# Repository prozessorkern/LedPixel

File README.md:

# LedPixel
Small devices to drive up to 10W RGB LEDs by DMX
There might be a possibility to use them als a LED Wall/Display with extreme high power :)

## there might be several versions of the pcb (and Firmware)
* a dev board version with an ATmega8 with USB Bootloader, a dip Switch and some additional Interfaces
* a RGBW version with 4 LED Drivers an a STM32 Controller with 16 bit PWM, an faster RS485 than DMX and an additional SPI Interface for addressing multiple devices
* a board for an external LED

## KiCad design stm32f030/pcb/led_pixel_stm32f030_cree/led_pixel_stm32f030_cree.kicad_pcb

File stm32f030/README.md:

# LedPixel stm32f030

* a more powerful version with 4 chanels for RGBW LEDs
* designed with a backplane bus for dynamic adressing of multiple devices
* capable of 16 bit pwm for better resolution

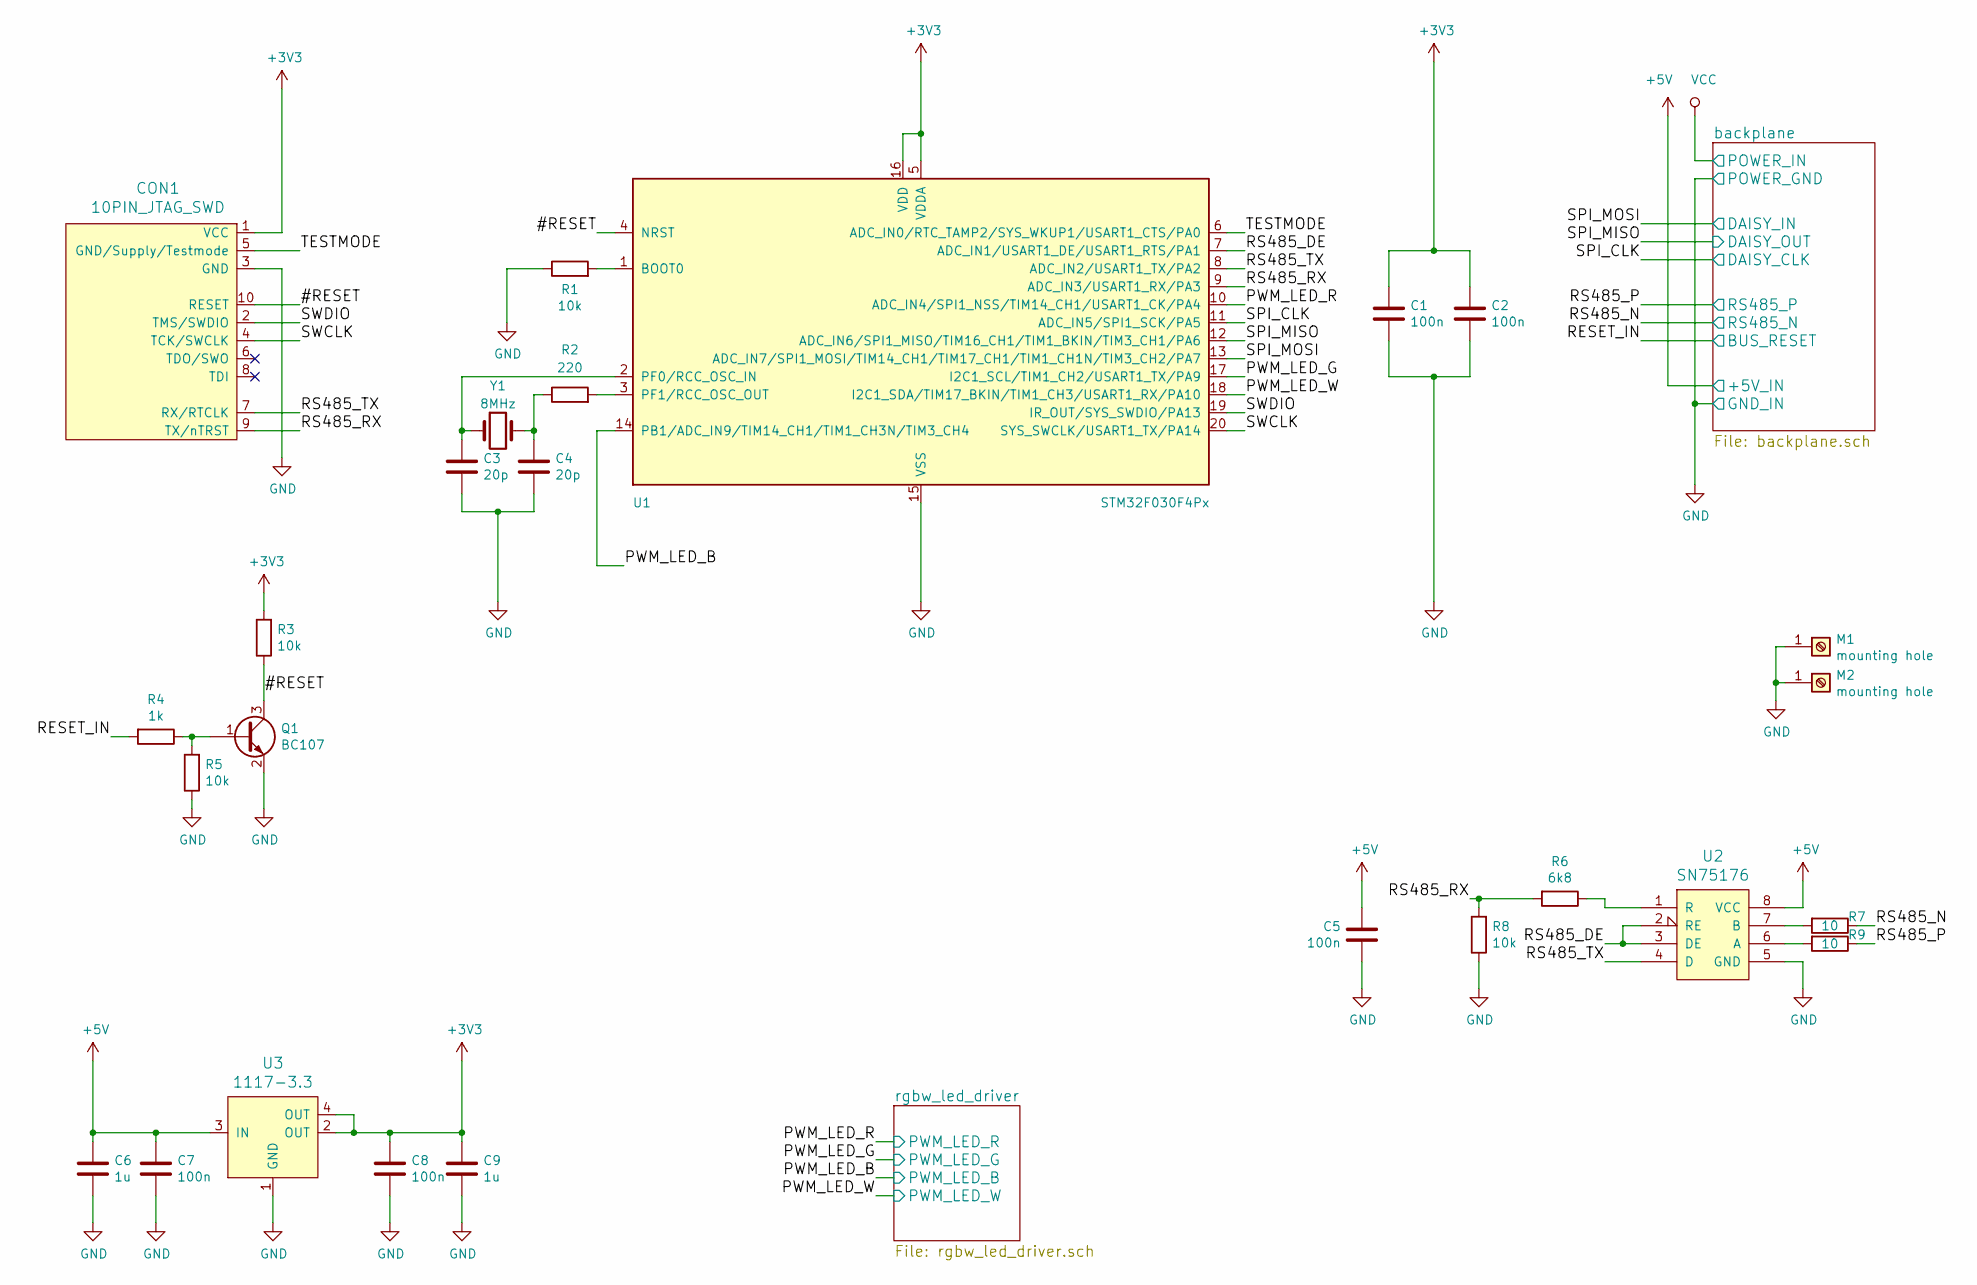
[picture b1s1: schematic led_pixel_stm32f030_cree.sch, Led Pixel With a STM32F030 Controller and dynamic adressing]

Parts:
C1, C2, C5, C7, C8: 100n; C_0603_HandSoldering
C3, C4: 20p; C_0603_HandSoldering
C6, C9: 1u; C_0603_HandSoldering
CON1: 10PIN_JTAG_SWD; TC2050-IDC
M1, M2: mounting hole; MountingHole_3.2mm_M3_Pad_Via
Q1: BC107; SOT-23
R1, R3, R5, R8: 10k; R_0603_HandSoldering
R2: 220; R_0603_HandSoldering
R4: 1k; R_0603_HandSoldering
R6: 6k8; R_0603_HandSoldering
R7, R9: 10; R_0603_HandSoldering
U1: STM32F030F4Px; TSSOP-20_4.4x6.5mm_Pitch0.65mm
U2: SN75176; SO-8
U3: 1117-3.3; SOT-223
Y1: 8MHz; Crystal_SMD_HC49-SD

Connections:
+3V3: C1.1, C2.1, C8.1, C9.1, CON1.1 (VCC), R3.2, U1.5 (VDDA), U1.16 (VDD), U3.2 (OUT), U3.4 (OUT)
+5V: C5.1, C6.1, C7.1, U2.8 (VCC), U3.3 (IN); also elsewhere on the board
/#RESET: CON1.10 (RESET), Q1.3 (C), R3.1, U1.4 (NRST)
/PWM_LED_B: U1.14 (PB1/ADC_IN9/TIM14_CH1/TIM1_CH3N/TIM3_CH4); also elsewhere on the board
/PWM_LED_G: U1.17 (I2C1_SCL/TIM1_CH2/USART1_TX/PA9); also elsewhere on the board
/PWM_LED_R: U1.10 (ADC_IN4/SPI1_NSS/TIM14_CH1/USART1_CK/PA4); also elsewhere on the board
/PWM_LED_W: U1.18 (I2C1_SDA/TIM17_BKIN/TIM1_CH3/USART1_RX/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); also elsewhere on the board
/RESET_IN: R4.2; also elsewhere on the board
/RS485_DE: U1.7 (ADC_IN1/USART1_DE/USART1_RTS/PA1), U2.2 (RE), U2.3 (DE)
/RS485_N: R7.1; also elsewhere on the board
/RS485_P: R9.1; also elsewhere on the board
/RS485_RX: CON1.9 (TX/nTRST), R6.2, R8.2, U1.9 (ADC_IN3/USART1_RX/PA3)
/RS485_TX: CON1.7 (RX/RTCLK), U1.8 (ADC_IN2/USART1_TX/PA2), U2.4 (D)
/SPI_CLK: U1.11 (ADC_IN5/SPI1_SCK/PA5); also elsewhere on the board
/SPI_MISO: U1.12 (ADC_IN6/SPI1_MISO/TIM16_CH1/TIM1_BKIN/T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); also elsewhere on the board
/SPI_MOSI: U1.13 (ADC_IN7/SPI1_MOSI/TIM14_CH1/TIM17_CH1/T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); also elsewhere on the board
/SWCLK: CON1.4 (TCK/SWCLK), U1.20 (SYS_SWCLK/USART1_TX/PA14)
/SWDIO: CON1.2 (TMS/SWDIO), U1.19 (IR_OUT/SYS_SWDIO/PA13)
/TESTMODE: CON1.5 (GND/Supply/Testmode), U1.6 (ADC_IN0/RTC_TAMP2/SYS_WKUP1/USART1_CTS/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)
GND: C1.2, C2.2, C3.2, C4.2, C5.2, C6.2, C7.2, C8.2, C9.2, CON1.3 (GND), M1.1, M2.1, Q1.2 (E), R1.1, R5.1, R8.1, U1.15 (VSS), U2.5 (GND), U3.1 (GND); also elsewhere on the board
unnamed: C3.1, U1.2 (PF0/RCC_OSC_IN), Y1.1
unnamed: C4.1, R2.1, Y1.2
unnamed: Q1.1 (B), R4.1, R5.2
unnamed: R1.2, U1.1 (BOOT0)
unnamed: R2.2, U1.3 (PF1/RCC_OSC_OUT)
unnamed: R6.1, U2.1 (R)
unnamed: R7.2, U2.7 (B)
unnamed: R9.2, U2.6 (A)

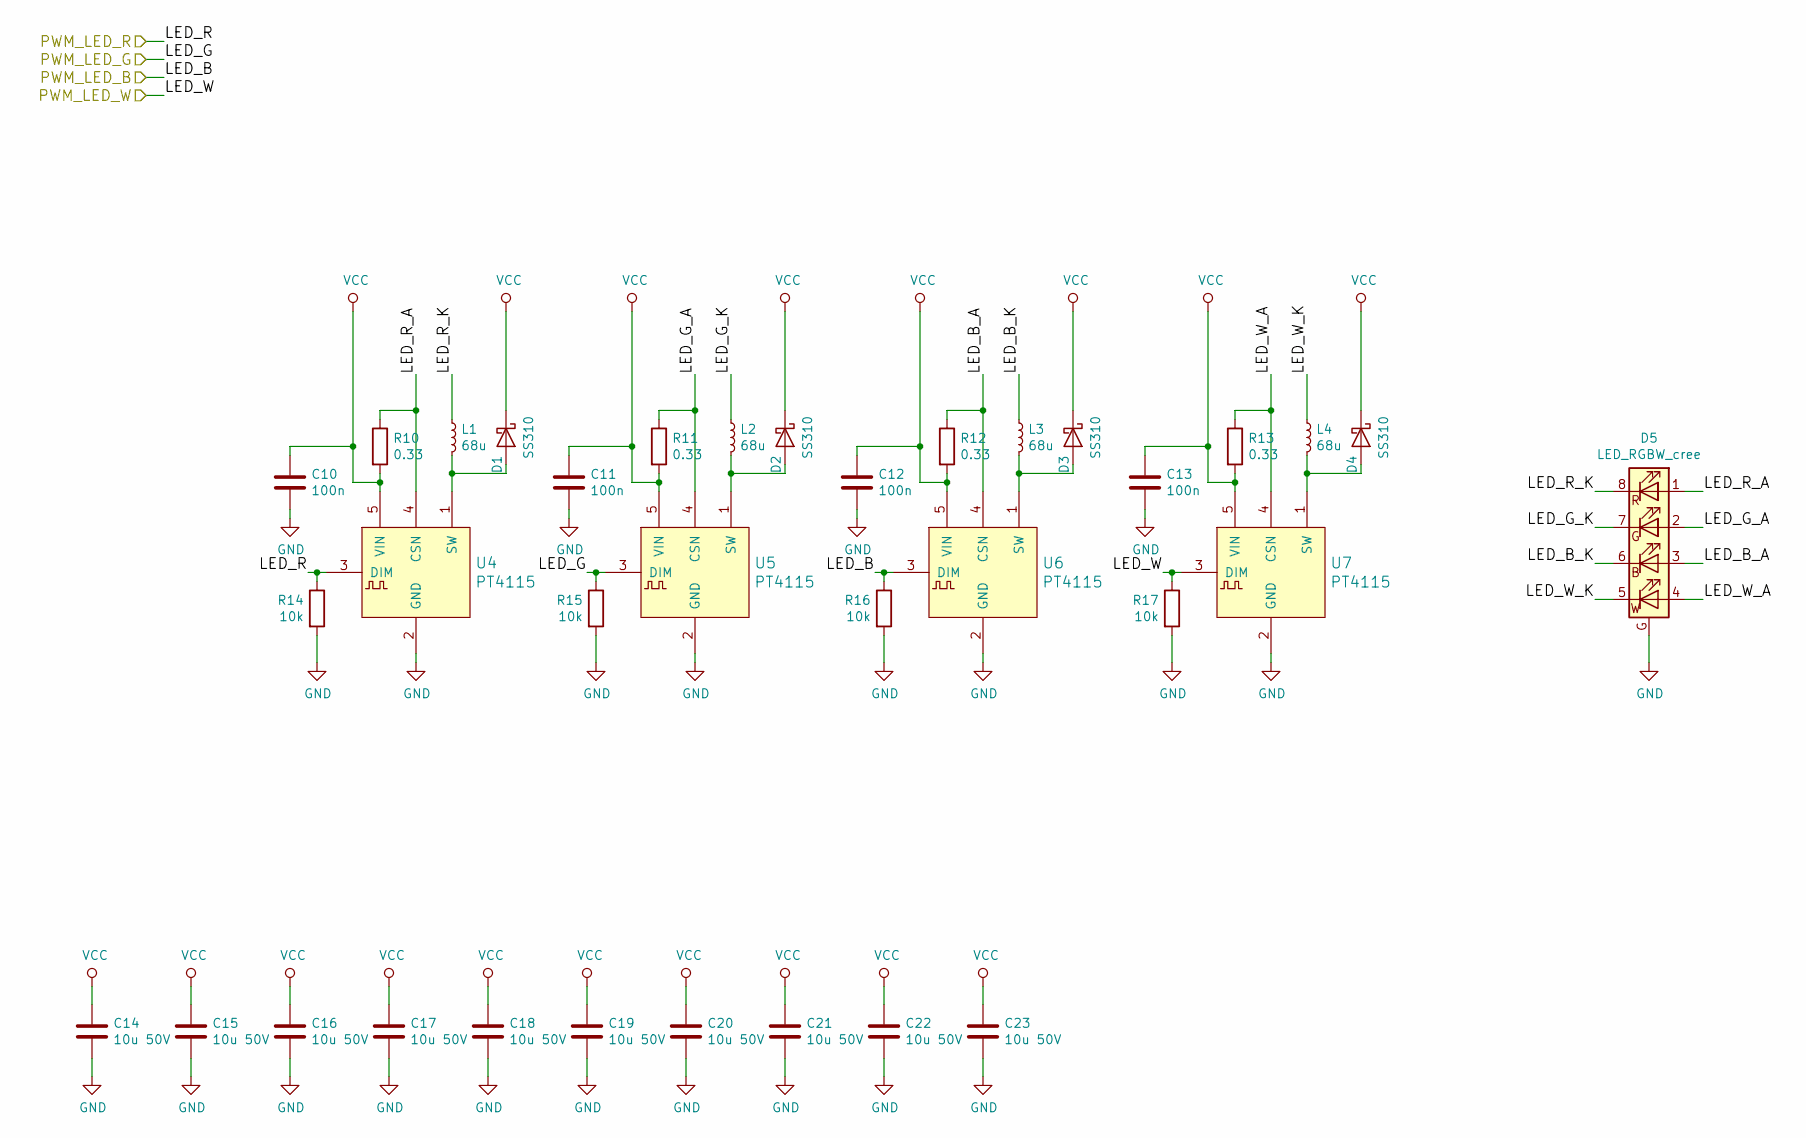
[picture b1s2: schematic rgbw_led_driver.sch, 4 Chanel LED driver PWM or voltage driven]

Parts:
C10, C11, C12, C13: 100n; C_0805_HandSoldering
C14, C15, C16, C17, C18, C19, C20, C21, C22, C23: 10u 50V; C_1210
D1, D2, D3, D4: SS310; D_SMA_Standard
D5: LED_RGBW_cree; LED_SMD_CREE_XM-L_4Color
L1, L2, L3, L4: 68u; Choke_SMD_4.5x4x3.2
R10, R11, R12, R13: 0.33; R_1206_HandSoldering
R14, R15, R16, R17: 10k; R_0603_HandSoldering
U4, U5, U6, U7: PT4115; SOT89-5_Housing_Handsoldering

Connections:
/PWM_LED_B: R16.1, U6.3 (DIM); also elsewhere on the board
/PWM_LED_G: R15.1, U5.3 (DIM); also elsewhere on the board
/PWM_LED_R: R14.1, U4.3 (DIM); also elsewhere on the board
/PWM_LED_W: R17.1, U7.3 (DIM); also elsewhere on the board
/rgbw_led_driver/LED_B_A: D5.3 (BK), R12.1, U6.4 (CSN)
/rgbw_led_driver/LED_B_K: D5.6 (BA), L3.1
/rgbw_led_driver/LED_G_A: D5.2 (GK), R11.1, U5.4 (CSN)
/rgbw_led_driver/LED_G_K: D5.7 (GA), L2.1
/rgbw_led_driver/LED_R_A: D5.1 (RK), R10.1, U4.4 (CSN)
/rgbw_led_driver/LED_R_K: D5.8 (RA), L1.1
/rgbw_led_driver/LED_W_A: D5.4 (WK), R13.1, U7.4 (CSN)
/rgbw_led_driver/LED_W_K: D5.5 (WA), L4.1
GND: C10.2, C11.2, C12.2, C13.2, C14.2, C15.2, C16.2, C17.2, C18.2, C19.2, C20.2, C21.2, C22.2, C23.2, D5.G (Thermal_Pad), R14.2, R15.2, R16.2, R17.2, U4.2 (GND), U5.2 (GND), U6.2 (GND), U7.2 (GND); also elsewhere on the board
unnamed: D1.2 (A), L1.2, U4.1 (SW)
unnamed: D2.2 (A), L2.2, U5.1 (SW)
unnamed: D3.2 (A), L3.2, U6.1 (SW)
unnamed: D4.2 (A), L4.2, U7.1 (SW)
VCC: C10.1, C11.1, C12.1, C13.1, C14.1, C15.1, C16.1, C17.1, C18.1, C19.1, C20.1, C21.1, C22.1, C23.1, D1.1 (K), D2.1 (K), D3.1 (K), D4.1 (K), R10.2, R11.2, R12.2, R13.2, U4.5 (VIN), U5.5 (VIN), U6.5 (VIN), U7.5 (VIN); also elsewhere on the board

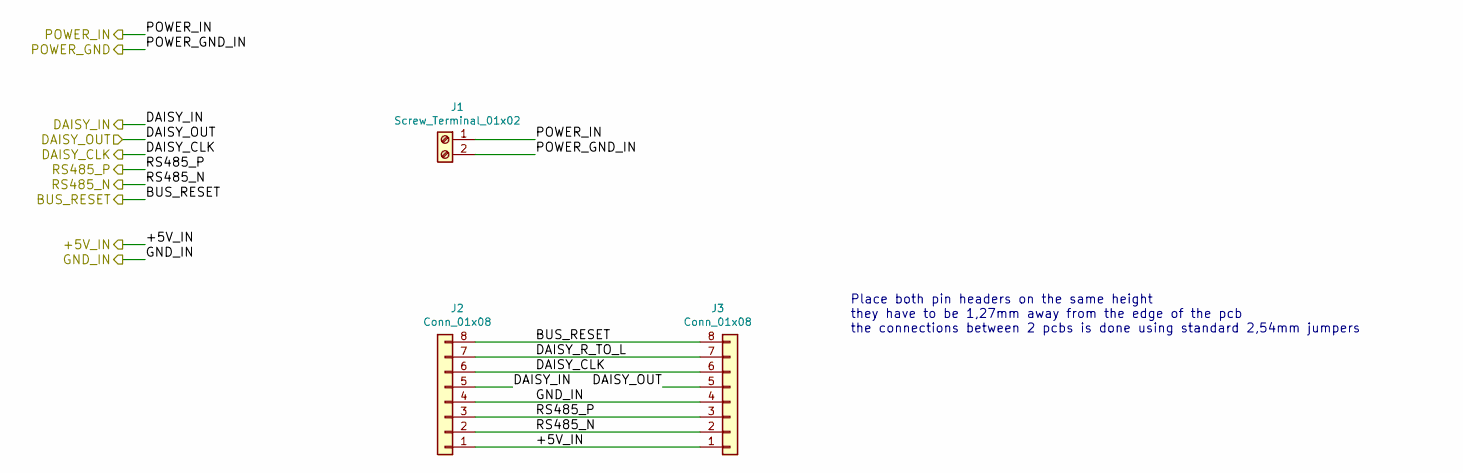
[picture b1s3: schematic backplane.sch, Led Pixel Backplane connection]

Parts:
J1: Screw_Terminal_01x02; AK300-2
J2, J3: Conn_01x08; Pin_Header_Straight_1x08_Pitch2.54mm

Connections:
+5V: J2.1, J3.1; also elsewhere on the board
/RESET_IN: J2.8, J3.8; also elsewhere on the board
/RS485_N: J2.2, J3.2; also elsewhere on the board
/RS485_P: J2.3, J3.3; also elsewhere on the board
/SPI_CLK: J2.6, J3.6; also elsewhere on the board
/SPI_MISO: J3.5; also elsewhere on the board
/SPI_MOSI: J2.5; also elsewhere on the board
/backplane/DAISY_R_TO_L: J2.7, J3.7
GND: J1.2, J2.4, J3.4; also elsewhere on the board
VCC: J1.1; also elsewhere on the board

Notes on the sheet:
Place both pin headers on the same height they have to be 1,27mm away from the edge of the pcb the connections between 2 pcbs is done using standard 2,54mm jumpers

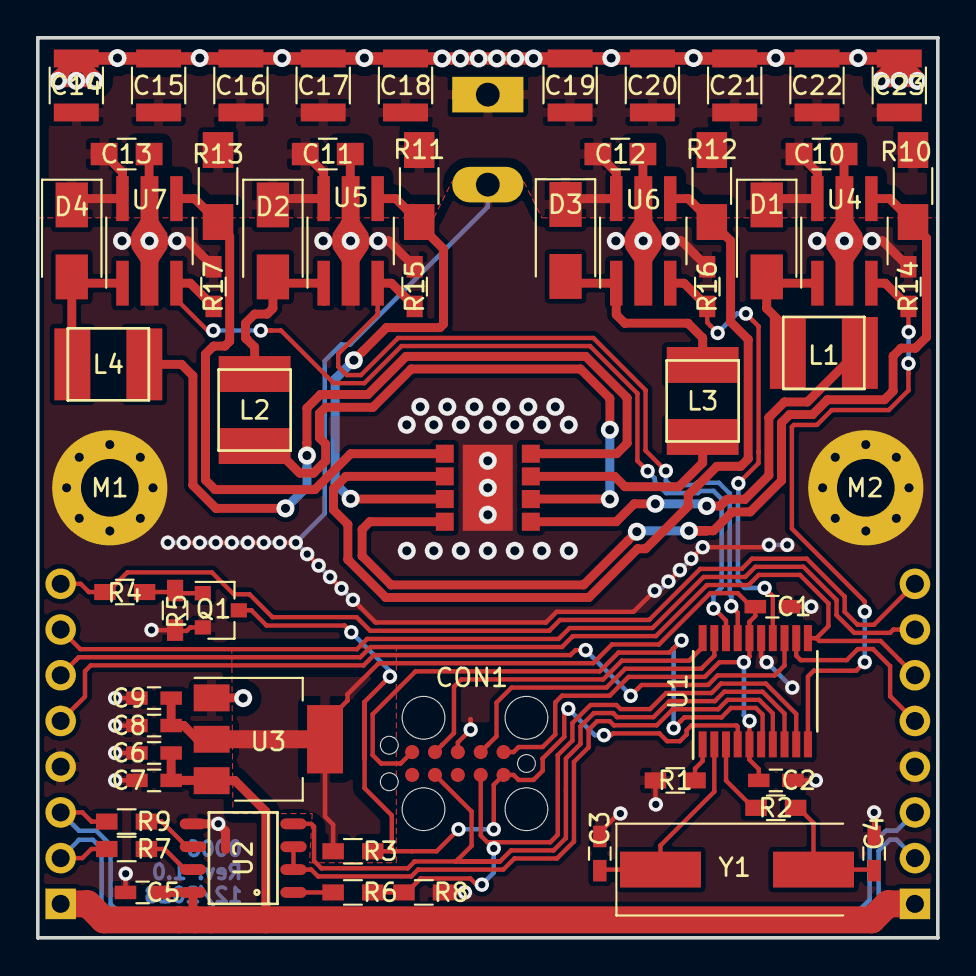
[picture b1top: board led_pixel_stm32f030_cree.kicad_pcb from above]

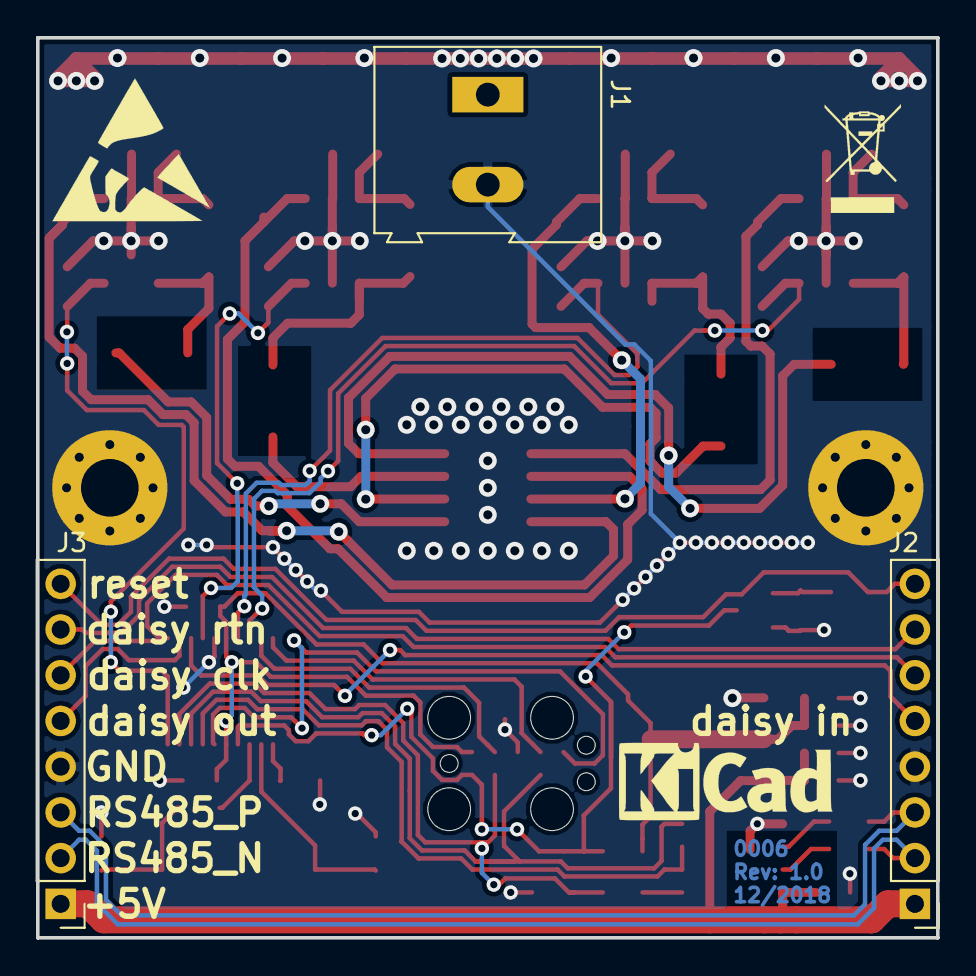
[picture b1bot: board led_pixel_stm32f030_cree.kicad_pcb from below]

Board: 2 copper layers, 50.0 x 50.0 mm, 64 parts (3 on the bottom side), 42 nets.

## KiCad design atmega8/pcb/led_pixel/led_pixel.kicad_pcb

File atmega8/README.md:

# LedPixel atmega8

* a dev board version with an ATmega8 with USB Bootloader, a dip Switch and some additional Interfaces
* designed to drive a 10W RGB LED with a single supply and DMX

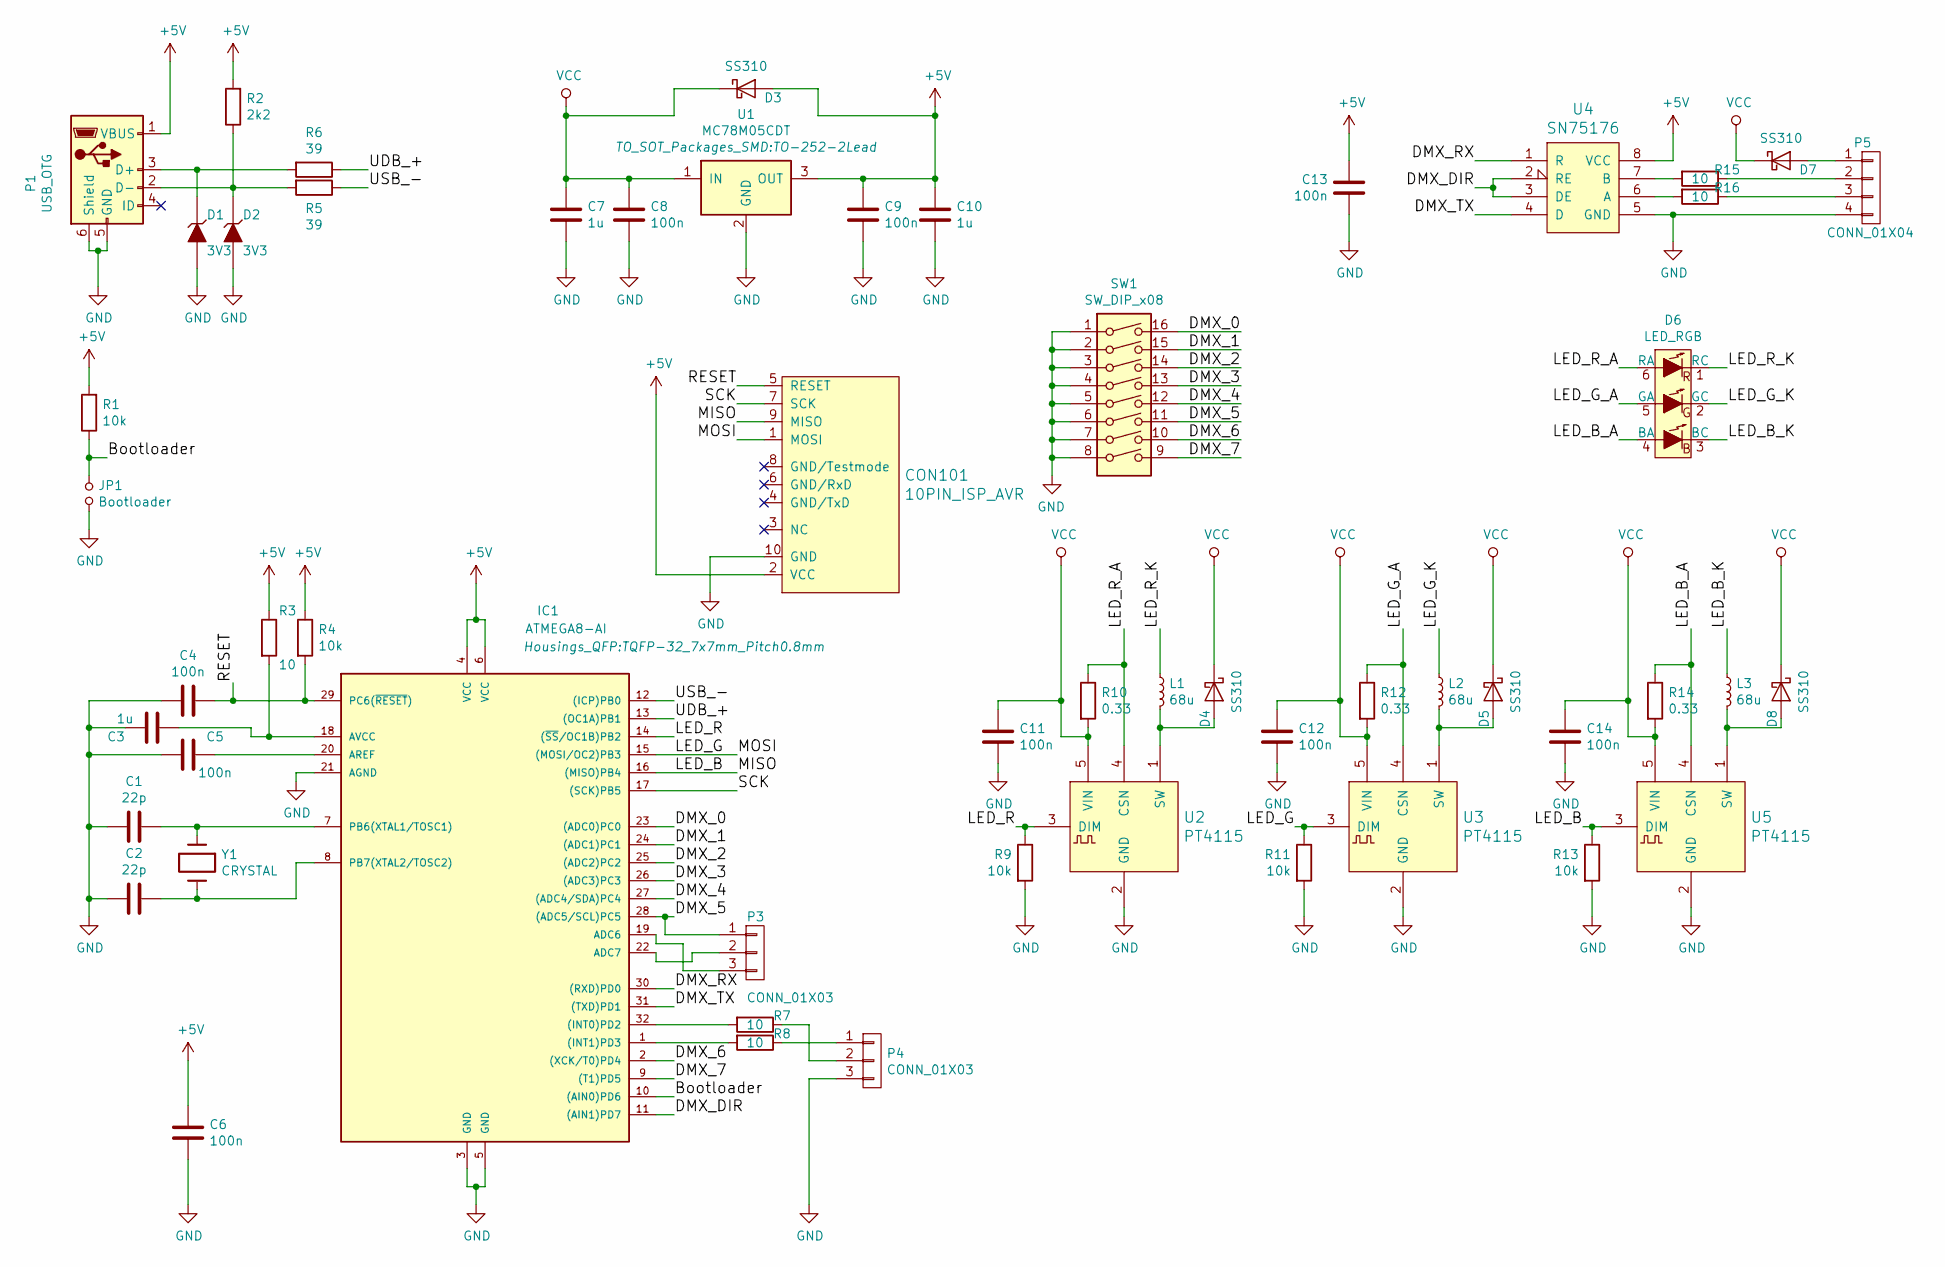
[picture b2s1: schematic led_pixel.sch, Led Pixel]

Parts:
C1, C2: 22p; C_0603_HandSoldering
C3, C10: 1u; C_0603_HandSoldering
C4, C5, C6, C9, C13: 100n; C_0603_HandSoldering
C7: 1u; C_0805_HandSoldering
C8, C11, C12, C14: 100n; C_0805_HandSoldering
CON101: 10PIN_ISP_AVR; TC2050-IDC
D1, D2: 3V3; D_MiniMELF_Standard
D3, D4, D5, D7, D8: SS310; D_SMA_Standard
D6: LED_RGB; LED_SMD_RGB_3W
IC1: ATMEGA8-AI; TQFP-32_7x7mm_Pitch0.8mm
JP1: Bootloader; Socket_Strip_Straight_1x02
L1, L2, L3: 68u; Choke_SMD_4.5x4x3.2
P1: USB_OTG; USB_Mini-B
P3, P4: CONN_01X03; Socket_Strip_Straight_1x03
P5: CONN_01X04; Socket_Strip_Straight_1x04
R1, R4, R9, R11, R13: 10k; R_0603_HandSoldering
R2: 2k2; R_0603_HandSoldering
R3, R7, R8, R15, R16: 10; R_0603_HandSoldering
R5, R6: 39; R_0603_HandSoldering
R10, R12, R14: 0.33; R_1206_HandSoldering
SW1: SW_DIP_x08; SW_DIP_x8_SMD_2.54
U1: MC78M05CDT; TO-252-2Lead
U2, U3, U5: PT4115; SOT89-5_Housing_Handsoldering
U4: SN75176; SO-8
Y1: CRYSTAL; Crystal_SMD_HC49-SD_HandSoldering

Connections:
+5V: C6.1, C9.1, C10.1, C13.1, CON101.2 (VCC), D3.2 (A), IC1.4 (VCC), IC1.6 (VCC), P1.1 (VBUS), R1.2, R2.2, R3.1, R4.1, U1.3 (OUT), U4.8 (VCC)
/Bootloader: IC1.10 ((AIN0)PD6), JP1.1, R1.1
/DMX_0: IC1.23 ((ADC0)PC0), SW1.16
/DMX_1: IC1.24 ((ADC1)PC1), SW1.15
/DMX_2: IC1.25 ((ADC2)PC2), SW1.14
/DMX_3: IC1.26 ((ADC3)PC3), SW1.13
/DMX_4: IC1.27 ((ADC4/SDA)PC4), SW1.12
/DMX_5: IC1.28 ((ADC5/SCL)PC5), P3.1, SW1.11
/DMX_6: IC1.2 ((XCK/T0)PD4), SW1.10
/DMX_7: IC1.9 ((T1)PD5), SW1.9
/DMX_DIR: IC1.11 ((AIN1)PD7), U4.2 (RE), U4.3 (DE)
/DMX_RX: IC1.30 ((RXD)PD0), U4.1 (R)
/DMX_TX: IC1.31 ((TXD)PD1), U4.4 (D)
/LED_B: CON101.9 (MISO), IC1.16 ((MISO)PB4), R13.1, U5.3 (DIM)
/LED_B_A: D6.4 (BA), R14.1, U5.4 (CSN)
/LED_B_K: D6.3 (BC), L3.1
/LED_G: CON101.1 (MOSI), IC1.15 ((MOSI/OC2)PB3), R11.1, U3.3 (DIM)
/LED_G_A: D6.5 (GA), R12.1, U3.4 (CSN)
/LED_G_K: D6.2 (GC), L2.1
/LED_R: IC1.14 ((~SS~/OC1B)PB2), R9.1, U2.3 (DIM)
/LED_R_A: D6.6 (RA), R10.1, U2.4 (CSN)
/LED_R_K: D6.1 (RC), L1.1
/RESET: C4.1, CON101.5 (RESET), IC1.29 (PC6(~RESET~)), R4.2
/SCK: CON101.7 (SCK), IC1.17 ((SCK)PB5)
/UDB_+: IC1.13 ((OC1A)PB1), R6.1
/USB_-: IC1.12 ((ICP)PB0), R5.1
GND: C1.2, C2.2, C3.2, C4.2, C5.2, C6.2, C7.2, C8.2, C9.2, C10.2, C11.2, C12.2, C13.2, C14.2, CON101.10 (GND), D1.2 (A), D2.2 (A), IC1.3 (GND), IC1.5 (GND), IC1.21 (AGND), JP1.2, P1.5 (GND), P1.6 (Shield), P4.3, P5.4, R9.2, R11.2, R13.2, SW1.1, SW1.2, SW1.3, SW1.4, SW1.5, SW1.6, SW1.7, SW1.8, U1.2 (GND), U2.2 (GND), U3.2 (GND), U4.5 (GND), U5.2 (GND)
unnamed: C1.1, IC1.7 (PB6(XTAL1/TOSC1)), Y1.1
unnamed: C2.1, IC1.8 (PB7(XTAL2/TOSC2)), Y1.2
unnamed: C3.1, IC1.18 (AVCC), R3.2
unnamed: C5.1, IC1.20 (AREF)
unnamed: D1.1 (K), P1.3 (D+), R6.2
unnamed: D2.1 (K), P1.2 (D-), R2.1, R5.2
unnamed: D4.2 (A), L1.2, U2.1 (SW)
unnamed: D5.2 (A), L2.2, U3.1 (SW)
unnamed: D7.2 (A), P5.1
unnamed: D8.2 (A), L3.2, U5.1 (SW)
unnamed: IC1.1 ((INT1)PD3), R8.2
unnamed: IC1.19 (ADC6), P3.3
unnamed: IC1.22 (ADC7), P3.2
unnamed: IC1.32 ((INT0)PD2), R7.2
unnamed: P4.1, R8.1
unnamed: P4.2, R7.1
unnamed: P5.2, R15.1
unnamed: P5.3, R16.1
unnamed: R15.2, U4.7 (B)
unnamed: R16.2, U4.6 (A)
VCC: C7.1, C8.1, C11.1, C12.1, C14.1, D3.1 (K), D4.1 (K), D5.1 (K), D7.1 (K), D8.1 (K), R10.2, R12.2, R14.2, U1.1 (IN), U2.5 (VIN), U3.5 (VIN), U5.5 (VIN)

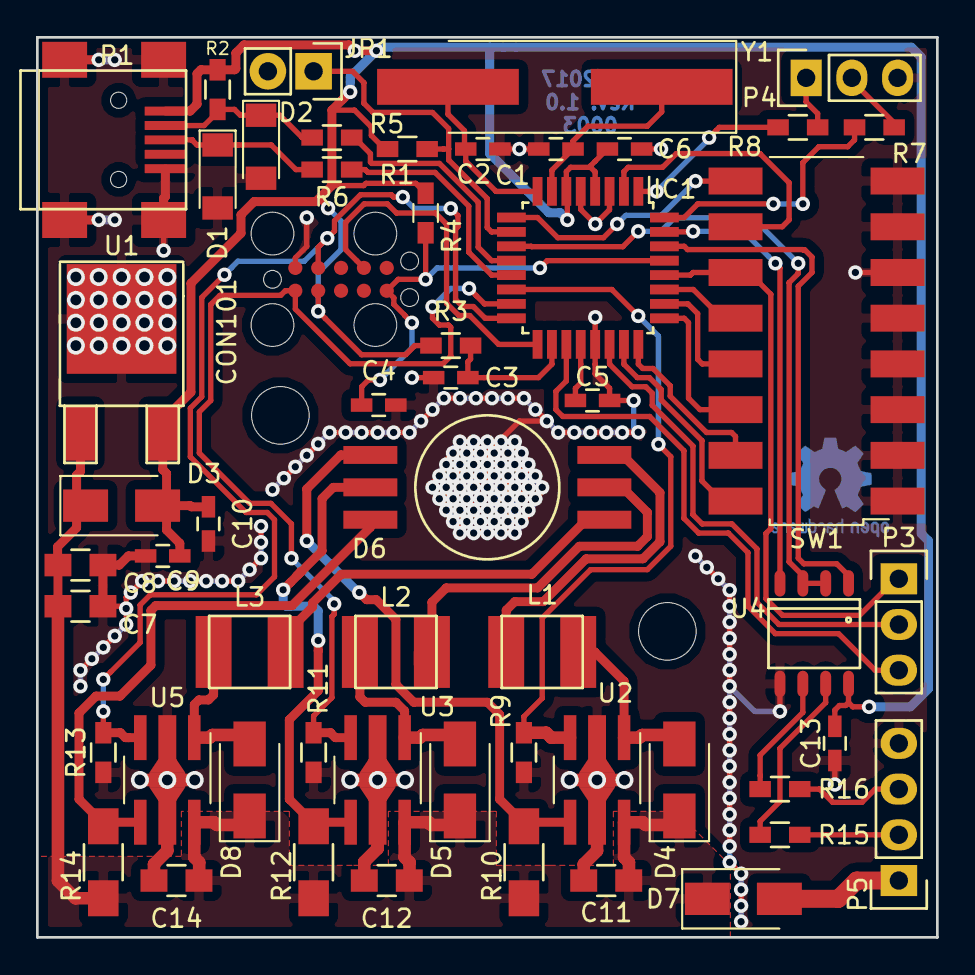
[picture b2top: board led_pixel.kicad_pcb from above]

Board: 2 copper layers, 50.0 x 50.0 mm, 55 parts (0 on the bottom side), 48 nets.

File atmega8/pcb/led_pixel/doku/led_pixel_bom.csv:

"ID";"Bezeichner";"Gehäuse";"Stückzahl";"Bezeichnung";"Anbieter und Ref.";
1;"Y1";"Crystal_SMD_HC49-SD_HandSoldering";1;"CRYSTAL";;;
2;"L3,L2,L1";"Choke_SMD_4.5x4x3.2";3;"68u";;;
3;"D6";"LED_SMD_RGB_3W";1;"LED_RGB";;;
4;"REF**,REF**";"MountingHole_3.2mm_M3_DIN965";2;"MountingHole_3.2mm_M3_DIN965";;;
5;"REF***";"OSHW-Logo2_7.3x6mm_Copper";1;"OSHW-Logo2_7.3x6mm_Copper";;;
6;"REF***";"WEEE-Logo_4.2x6mm_SilkScreen";1;"WEEE-Logo_4.2x6mm_SilkScreen";;;
7;"REF**";"Symbol_KiCAD-Logo_CopperAndSilkScreenTop";1;"KiCAD Logo";;;
8;"G***";"Shimatta_SolderMask";1;"LOGO";;;
9;"C1,C2";"C_0603_HandSoldering";2;"22p";;;
10;"C3,C10";"C_0603_HandSoldering";2;"1u";;;
11;"C4,C5,C6,C9,C13";"C_0603_HandSoldering";5;"100n";;;
12;"C7";"C_0805_HandSoldering";1;"1u";;;
13;"C8,C11,C12,C14";"C_0805_HandSoldering";4;"100n";;;
14;"IC1";"TQFP-32_7x7mm_Pitch0.8mm";1;"ATMEGA8-AI";;;
15;"P1";"USB_Mini-B";1;"USB_OTG";;;
16;"R1,R9,R11,R13,R4";"R_0603_HandSoldering";5;"10k";;;
17;"R2";"R_0603_HandSoldering";1;"2k2";;;
18;"R3,R7,R8,R15,R16";"R_0603_HandSoldering";5;"10";;;
19;"R5,R6";"R_0603_HandSoldering";2;"39";;;
20;"R10,R12,R14";"R_1206_HandSoldering";3;"0.33";;;
21;"U1";"TO-252-2Lead";1;"MC78M05CDT";;;
22;"JP1";"Socket_Strip_Straight_1x02";1;"Bootloader";;;
23;"P3,P4";"Socket_Strip_Straight_1x03";2;"CONN_01X03";;;
24;"P5";"Socket_Strip_Straight_1x04";1;"CONN_01X04";;;
25;"U2,U3,U5";"SOT89-5_Housing_Handsoldering";3;"PT4115";;;
26;"U4";"SO-8";1;"SN75176";;;
27;"SW1";"SW_DIP_x8_SMD_2.54";1;"SW_DIP_x08";;;
28;"D1,D2";"D_MiniMELF_Standard";2;"3V3";;;
29;"D3,D4,D5,D7,D8";"D_SMA_Standard";5;"SS310";;;
30;"CON101";"TC2050-IDC";1;"10PIN_ISP_AVR";;;

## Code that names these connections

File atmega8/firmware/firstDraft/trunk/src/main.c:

/*
 * main.c
 *
 * Created: 23.04.2017
 *  Author: Prozessorkern
 * 
 * receives a DMX Stream over UART and controls a RGB LED via soft PWM
 *
 */ 
/*
PORTB:

PB0: USB -
PB1: USB +
PB2: LED_R
PB3: LED_G
PB4: LED_B
PB5: NC

PORTC:

PC0: Dip 0
PC1: Dip 1
PC2: Dip 2
PC3: Dip 3
PC4: Dip 4
PC5: Dip 5

PORTD:

PD0: DMX Receive
PD1: DMX Send
PD2: GPIO1
PD3: GPIO2
PD4: Dip 6
PD5: Dip 7
PD6: Bootloader
PD7: DMX_DIR

*/

#define F_CPU 16000000
#define MAX_BRIGHTNES 200

#include <avr/io.h>
#include <util/delay.h>  
#include <avr/interrupt.h> 
#include <stdlib.h>


uint8_t volatile channel[3] = {0,0,0};

int main(void)
{	
	int16_t current_byte = 2;
	uint8_t current_bit = -1;
	int16_t adress;
	int16_t status = 0;
	uint16_t counter = 0;
	uint8_t color = 0;
	uint8_t color_counter = 0;

	DDRB = 0b00011100;
	PORTB = 0b000000000;
	DDRC = 0x00;
	PORTC = 0xFF;
	DDRD = 0b10000010;
	PORTD = 0b00110000;
	
	/*! - enable UART reception */
	UBRRL  = ((F_CPU/4000000)-1);						//250kbaud, 8N2
	UCSRC  = (1<<URSEL)|(3<<UCSZ0)|(1<<USBS);

	UCSRB  = (1<<RXEN);
	
	/*! - configure timer1 */
	TCCR1B = (1<<WGM12)|(1<<CS10);
	OCR1A = 150;
	TIMSK |= (1<<OCIE1A);
	
	/*! - calculate DMX address */
	adress = 256 - (PINC + ((PIND<<2)&0b11000000));

	/*! - reset counter 1 */
	TCNT1 = 0;
	
	/*! - enable interrupts for soft - pwm */
	sei();
	
	while(!(UCSRA & (1<<RXC)))
	{
		counter ++;
		if(counter > 13000)
		{
			counter = 0;
			
			if(color_counter < 255)
			{
				color_counter ++;
			}
			else
			{
				color_counter = 0;
				color ++;
				channel[0] = 0;
				channel[1] = 0;
				channel[2] = 0;
			}
			
			if(!(color & 0x07))
			{
				color ++;
				channel[0] = 0;
				channel[1] = 0;
				channel[2] = 0;
			}
			
			if(color & 0b00000001u)
			{
				channel[0] ++;
			}
			else
			{
				channel[0] = 0u;
			}
			
			if(color & 0b00000010u)
			{
				channel[1] ++;
			}
			else
			{
				channel[1] = 0u;
			}
			
			if(color & 0b00000100u)
			{
				channel[2] ++;
			}
			else
			{
				channel[2] = 0u;
			}

		}			
			
	}
	
	channel[0] = 0;
	channel[1] = 0;
	channel[2] = 0;
	
    while(1)
    {
		/*! - wait for incominc UART Frame (DMX) */
		while(!(UCSRA & (1<<RXC)))
		{
			asm volatile("nop");
		}
		/*! - get status and data from UART controler */
		status = UCSRA;
		current_bit = UDR;
			
		/*! - check for UART framing error ==> DMX pause detected */
		if((status & (1<<FE))){
			current_byte = 1;
			UCSRA &= ~(1<<FE);
		}
		
		/*! - check for first DMX Byte ==> allways 0 */
		else if(current_byte == 1){	
			/* no error */
			if(current_bit == 0)
			{
				current_byte = 2;
			}
			/* error */
			else
			{
				current_byte = -2;
			}	
		}
		
		/*! - check if received DMX date has our address */
		else if(current_byte >= adress && current_byte <=(adress+2)){
			
			/*! - copy data */
			channel[current_byte - adress] = current_bit;
			current_byte ++;
				
		}
		
		/*! - not our address */
		else if(current_byte > 0 && current_byte <= 255)
		{
			current_byte ++;
		}
		
		/*! - DMX address exceeded range ==> stop reception until pause is received */
		else
		{
			current_byte = -2;
		}
		
		/*! - delete UART status */
		UCSRA = 0;
    }
}

/* Timer interrupt handler for soft pwm */
ISR(TIMER1_COMPA_vect){
	
	static uint8_t counter = 0;

	/*! - overflow detected */
	if(counter > 254){
		/*! - reset counter and set outputs if active */
		counter = 0;
		PORTB &= ~((1<<PB2)&(1<<PB3)&(1<<PB4));
		
		if(channel[0] > 0) PORTB |= (1<<PB4);
		if(channel[1] > 0) PORTB |= (1<<PB3);
		if(channel[2] > 0) PORTB |= (1<<PB2);
		
	}
	else{
		/*! - increment counter */
		counter ++;
		
		/*! - reset outputs if nessesary*/
		if(channel[0] < counter) PORTB &= ~(1<<PB4);
		if(channel[1] < counter) PORTB &= ~(1<<PB3);
		if(channel[2] < counter) PORTB &= ~(1<<PB2);
	}

}

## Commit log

2017-02-06 Initial Commit of existing Files
2017-02-10 chaned README.md
2017-02-12 layout in process... :|
2017-02-20 finished first shot of the layout...
    there are mounting holes missing...
    ...so what ;)
    I hope to find a place for them this week...
2017-03-13 Test Commit
2017-04-16 finished rought layout with mounting holes and needle debug adaptor...
2017-04-16 finished... I hope...
    replaced the ref descriptors...
2017-04-16 did some final fixes...
    created doku package and gerber files...
    ready for chinese PCB production ;)
2017-04-16 ...forget to save layout...
2017-04-23 generated documentation and gerber files
2017-04-23 added a first draft firmware to test some parts of the hardware
    the makefile is crap and has to be improved
    programming is not working right now...
    you will need the avr8 toolchain from Atmel
2017-04-23 added flashing function to makefile usind AVRdude
    added a standalone test function which gets deactivated once there is a DMX signal
2017-04-23 startet with development of stm32f0 powered led pixel
    rough schematics with some of the parts needed
    definition of the backplane bus system is pending
2017-04-23 changed Makefile:
    - changed compiler optimization
    - added the makedile itself to the dependencies of the objects
2017-04-30 designed a first draft of the backplane of the dynamic adressing LED Pixels
    started with pcb design of the STM32 version
2017-05-01 made a first layout draft...
    well okay, wouldn´t call it layout yet ;)
    - next step make it look like a Layout XD
2017-05-01 added mounting holes
    added a lot of capacitors (there was some room left ;) )
    layout nearly finished
    logos are missing ;)
    not much work left I think
2017-05-07 finished layout for stm32f0 version
    the silkscreen has to be fixed...
    documentation and production data has to be generated
2017-05-10 hopefully finished everything
    generated documentation and gerber files
2017-05-13 added pcb number and revision
    re generated all docu and gerber data
    - ordered this one as rev 1.0
2017-06-18 updraded to revision V1.1
    Now the cooling pad of the LED is isolated from the ground plane.
    Unfortunately there will be less cooling than before, but the LEDs to use have a stupid connection...
2018-12-24 final release of cree led version v1.0
2019-08-27 added x4 version
2019-08-27 added archive
